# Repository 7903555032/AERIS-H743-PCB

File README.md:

# AERIS-H743 Hardware

# AERIS — Advanced Embedded Research & Intelligent Systems

A 6-layer STM32H743-based embedded development and flight-control/data-logging PCB designed as a practical hardware-design and PCB-layout project.

## Project Status

🚧 **Practice / Learning Project — Hardware Design Completed**

The PCB design phase is complete. This project is primarily a practical exercise to learn and apply professional PCB design concepts using KiCad, including schematic design, component selection, multi-layer stackup, component placement, power distribution, signal routing, high-speed interfaces, sensor interfacing, and design-rule checking.

This is **not a production-ready or professionally validated flight controller**. The design may contain mistakes or areas that require further review, optimization, and hardware validation.

The main goal of this project is to gain hands-on experience designing a complex **6-layer embedded PCB** from the ground up.

## Hardware Features

- STM32H743VIT6 — ARM Cortex-M7, up to 480 MHz
- 6-Layer PCB
- USB Type-C
- SPI / QSPI External Flash
- microSD via SDMMC
- ICM-42688-P IMU
- BME280 Environmental Sensor
- RTC
- INA219 Power Monitor
- CAN FD
- RS485
- GPS UART
- 4× ESC PWM Outputs
- SWD Debug Interface
- 3.3 V / 5 V Regulated Power Architecture

## PCB Architecture

- **L1 — Components + Critical Signals**
- **L2 — Ground Plane**
- **L3 — Power Distribution**
- **L4 — Signal Routing**
- **L5 — Ground Plane**
- **L6 — Bottom Signals + Selected Components**

## Communication Interfaces

- CAN FD
- RS485
- GPS UART
- USB
- SPI / QSPI
- I²C
- SDMMC

## PCB Design Goals

The main purpose of this project is to practice designing a relatively complex embedded PCB and understand how different parts of a real hardware system interact.

The design focuses on:

- 6-layer PCB architecture
- Power distribution
- Ground-plane design
- High-speed digital interfaces
- MCU placement and routing
- Sensor placement
- IMU placement considerations
- QSPI and SDMMC routing
- USB differential-pair routing
- CAN FD and RS485 interfaces
- ESC interfaces
- Thermal and mechanical considerations
- Custom KiCad symbols, footprints and 3D models
- PCB Design Rule Checking (DRC)
- Manufacturing preparation

## Project Structure

```text
AERIS-H743/
│
├── KiCAD/
│   └── AERIS-H743-PCB/
│       ├── AERIS-H743-PCB.kicad_pro
│       ├── AERIS-H743-PCB.kicad_sch
│       ├── AERIS-H743-PCB.kicad_pcb
│       ├── MCU_Core.kicad_sch
│       ├── POWER.kicad_sch
│       ├── Memory&Storage.kicad_sch
│       └── sensors.kicad_sch
│
├── Libraries/
│   ├── Symbols/
│   ├── Footprints.pretty/
│   └── 3D/
│
├── Documentation/
│
├── Datasheets/
│
└── README.md

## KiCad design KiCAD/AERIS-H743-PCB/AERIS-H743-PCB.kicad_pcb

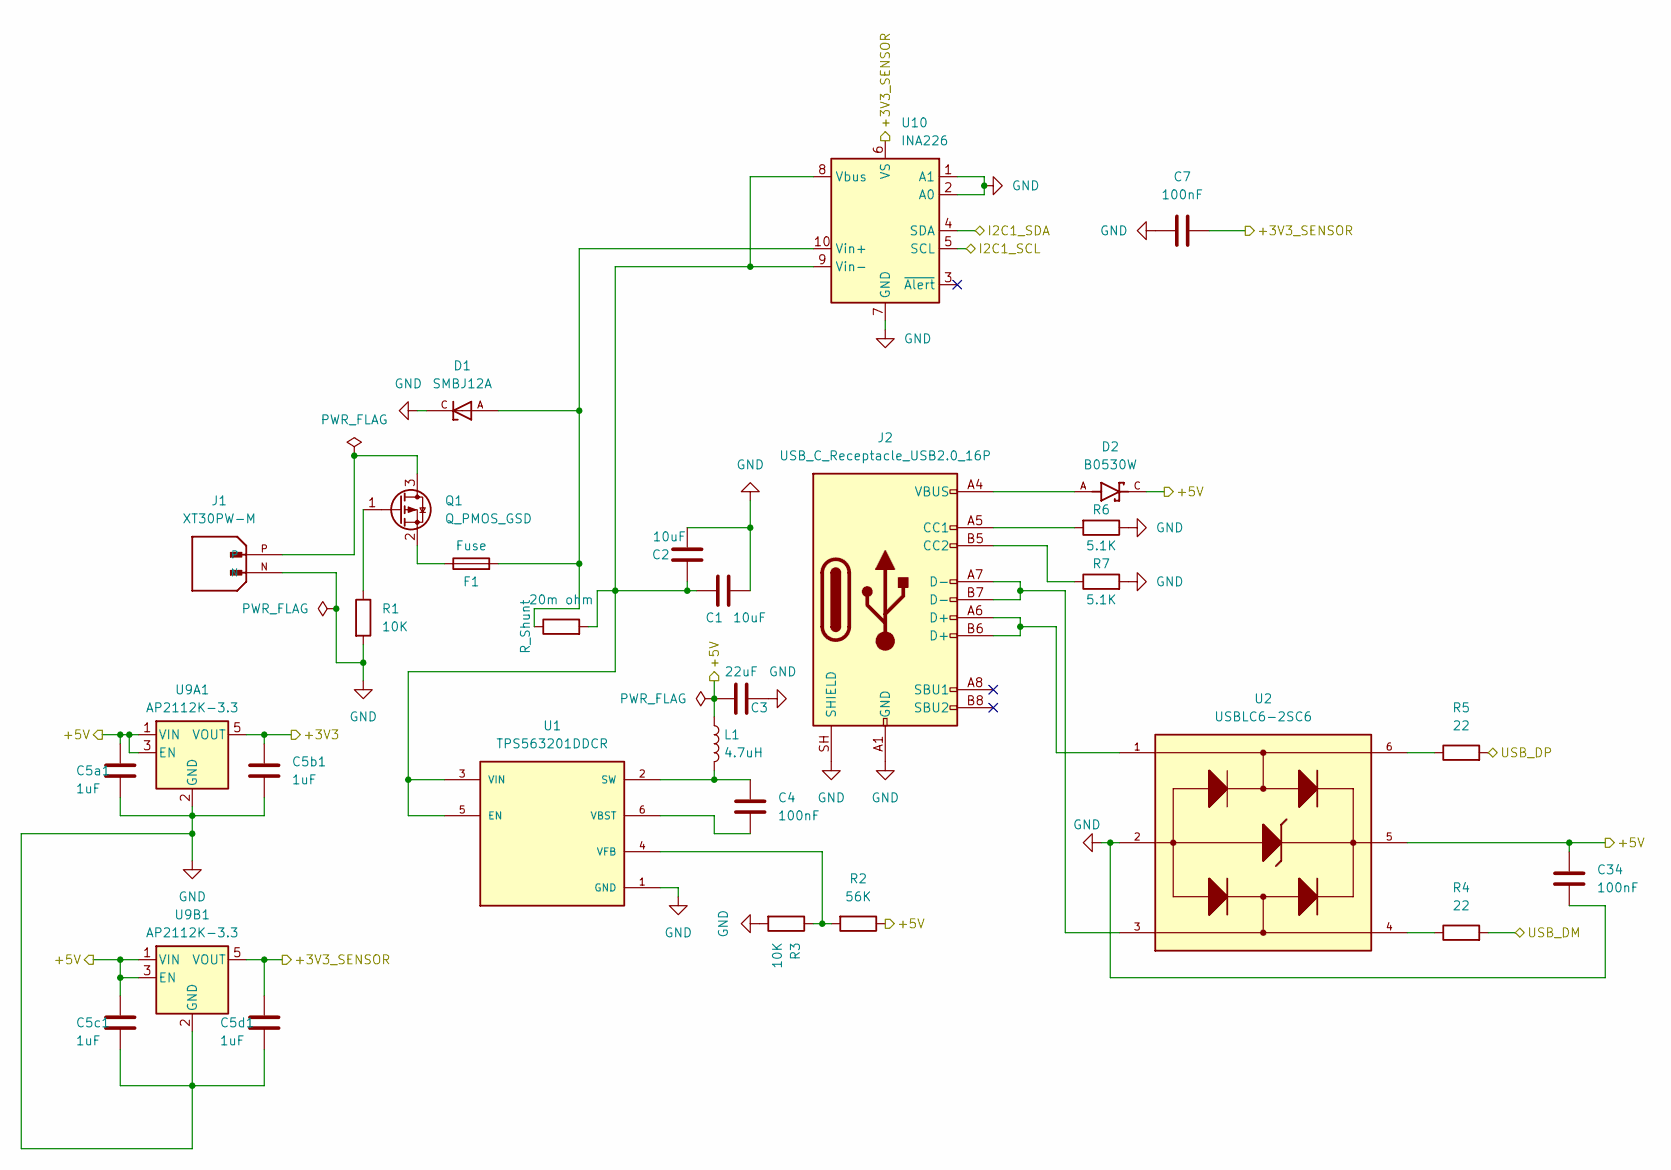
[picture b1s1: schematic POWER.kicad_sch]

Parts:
C1, C2: 10uF; C_0805_2012Metric
C3: 22uF; C_0805_2012Metric
C4, C7: 100nF; C_0805_2012Metric
C5a1, C5b1, C5c1, C5d1: 1uF; C_0805_2012Metric
C34: 100nF; C_0603_1608Metric
D1: SMBJ12A; DIOM4336X265N; PARTREV F2102
D2: B0530W; DIO_B0530W; PARTREV J2112
F1: Fuse; Fuse_1206_3216Metric
J1: XT30PW-M; PARTREV 1.2
J2: USB_C_Receptacle_USB2.0_16P; USB_C_Receptacle_GCT_USB4085
L1: 4.7uH; L_1210_3225Metric
Q1: Q_PMOS_GSD; SOT-23
R1, R3: 10K; R_0603_1608Metric
R2: 56K; R_0603_1608Metric
R4, R5: 22; R_0603_1608Metric
R6, R7: 5.1K; R_0603_1608Metric
R26: 20m ohm; R_2512_6332Metric
U1: TPS563201DDCR; SOT95P280X110-6N; PARTREV December 2015
U2: USBLC6-2SC6; SOT95P280X145-6N
U9A1: AP2112K-3.3; SOT-23-5
U9B1: AP2112K-3.3; SOT95P285X145-5N
U10: INA226; TSSOP-10_3x3mm_P0.5mm

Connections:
/3.3: C5b1.1, U9A1.5 (VOUT); also elsewhere on the board
/3.3_Sensor: C5d1.1, C7.1, U9B1.5 (VOUT), U10.6 (VS); also elsewhere on the board
/I2C1_SCL: U10.5 (SCL); also elsewhere on the board
/I2C1_SDA: U10.4 (SDA); also elsewhere on the board
/USB_DM: R4.2; also elsewhere on the board
/USB_DP: R5.2; also elsewhere on the board
unnamed: D2.A, J2.A4 (VBUS), J2.A9 (VBUS), J2.B4 (VBUS), J2.B9 (VBUS)
unnamed: J2.A5 (CC1), R6.2
unnamed: J2.B5 (CC2), R7.1
unnamed 66: J2.A6 (D+), J2.B6 (D+), U2.1; also elsewhere on the board
unnamed: J1.P, Q1.3 (D)
unnamed: Q1.1 (G), R1.1
unnamed: F1.1, Q1.2 (S)
unnamed 73: R5.1, U2.6; also elsewhere on the board
unnamed 74: C1.1, C2.2, R26.2, U1.3 (VIN), U1.5 (EN), U10.8 (Vbus), U10.9 (Vin-); also elsewhere on the board
unnamed: C4.1, L1.2, U1.2 (SW)
unnamed: C4.2, U1.6 (VBST)
unnamed: R2.2, R3.1, U1.4 (VFB)
unnamed 81: D1.A, F1.2, R26.1, U10.10 (Vin+); also elsewhere on the board

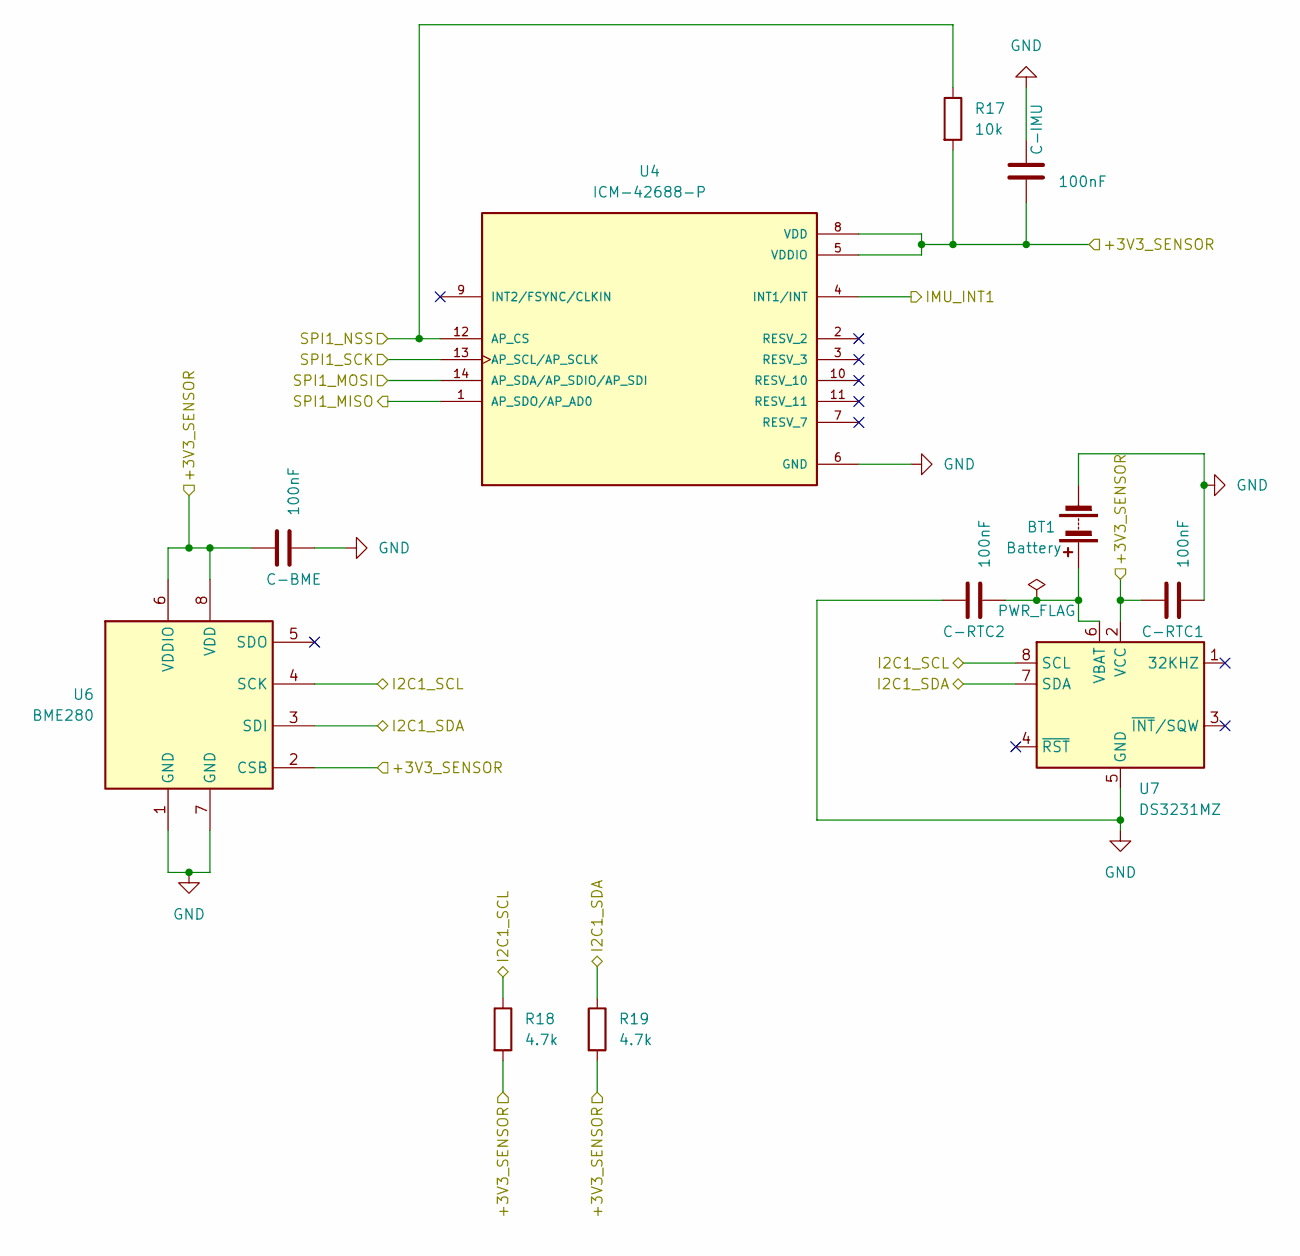
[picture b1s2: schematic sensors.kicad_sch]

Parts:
BT1: Battery; BatteryHolder_Keystone_1058_1x2032
C27, C28, C29, C30: 100nF; C_0603_1608Metric
R17: 10k; R_0603_1608Metric
R18, R19: 4.7k; R_0603_1608Metric
U4: ICM-42688-P; LGA-14_3x2.5mm_P0.5mm_LayoutBorder3x4y; PARTREV 1.2
U6: BME280; Bosch_LGA-8_2.5x2.5mm_P0.65mm_ClockwisePinNumbering
U7: DS3231MZ; SOIC-8_3.9x4.9mm_P1.27mm

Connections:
/3.3_Sensor: C27.2, C28.1, C29.1, R17.2, R18.2, R19.2, U4.5 (VDDIO), U4.8 (VDD), U6.2 (CSB), U6.6 (VDDIO), U6.8 (VDD), U7.2 (VCC); also elsewhere on the board
/I2C1_SCL: R18.1, U6.4 (SCK), U7.8 (SCL); also elsewhere on the board
/I2C1_SDA: R19.1, U6.3 (SDI), U7.7 (SDA); also elsewhere on the board
/IMU_INT1: U4.4 (INT1/INT); also elsewhere on the board
/MCU_Core/SPI1_MISO: U4.1 (AP_SDO/AP_AD0); also elsewhere on the board
/MCU_Core/SPI1_MOSI: U4.14 (AP_SDA/AP_SDIO/AP_SDI); also elsewhere on the board
/MCU_Core/SPI1_NSS: R17.1, U4.12 (AP_CS); also elsewhere on the board
/MCU_Core/SPI1_SCK: U4.13 (AP_SCL/AP_SCLK); also elsewhere on the board
unnamed: BT1.1 (+), C30.2, U7.6 (VBAT)

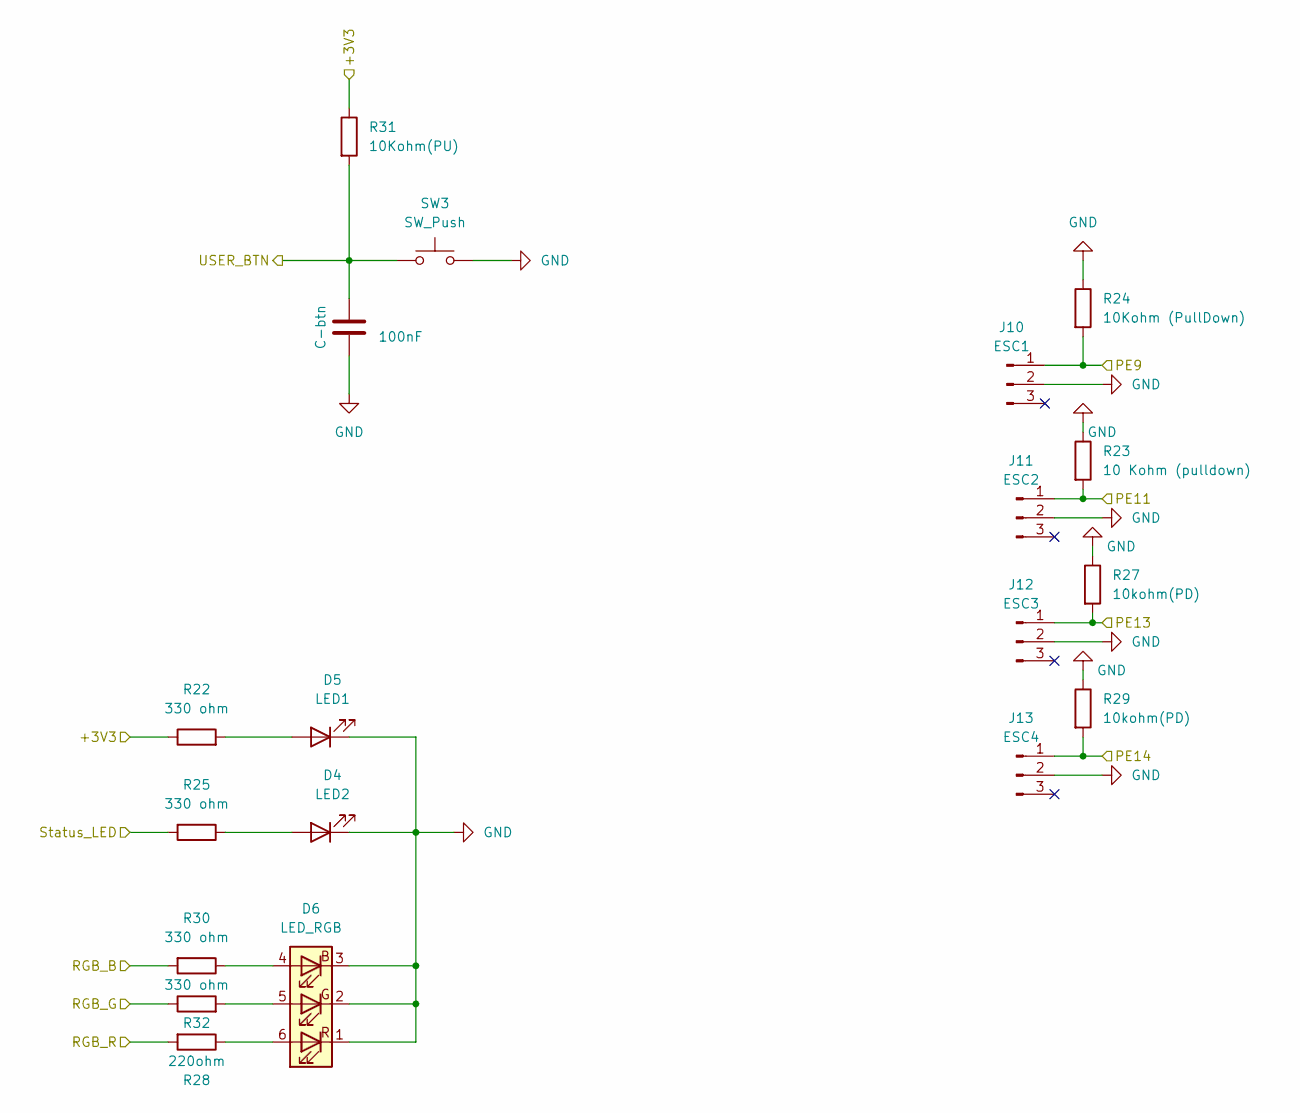
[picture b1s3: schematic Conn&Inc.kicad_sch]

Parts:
C33: 100nF; C_0603_1608Metric
D4: LED2; LED_0603_1608Metric
D5: LED1; LED_0603_1608Metric
D6: LED_RGB; LED_RGB_5050-6
J10: ESC1; PinHeader_1x03_P2.54mm_Vertical
J11: ESC2; PinHeader_1x03_P2.54mm_Vertical
J12: ESC3; PinHeader_1x03_P2.54mm_Vertical
J13: ESC4; PinHeader_1x03_P2.54mm_Vertical
R22, R25, R30, R32: 330 ohm; R_0603_1608Metric
R23: 10 Kohm (pulldown); R_0603_1608Metric
R24: 10Kohm (PullDown); R_0603_1608Metric
R27, R29: 10kohm(PD); R_0603_1608Metric
R28: 220ohm; R_0603_1608Metric
R31: 10Kohm(PU); R_0603_1608Metric
SW3: SW_Push; SW_SPST_B3U-1000P

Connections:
/3.3: R22.1, R31.1; also elsewhere on the board
/PE9: J10.1, R24.2; also elsewhere on the board
/PE11: J11.1, R23.2; also elsewhere on the board
/PE13: J12.1, R27.2; also elsewhere on the board
/PE14: J13.1, R29.2; also elsewhere on the board
/RGB_B: R30.2; also elsewhere on the board
/RGB_G: R32.1; also elsewhere on the board
/RGB_R: R28.2; also elsewhere on the board
/S_LED: R25.2; also elsewhere on the board
/U_BTN: C33.1, R31.2, SW3.1; also elsewhere on the board
unnamed: D4.2 (A), R25.1
unnamed: D5.2 (A), R22.2
unnamed: D6.4 (BA), R30.1
unnamed: D6.5 (GA), R32.2
unnamed: D6.6 (RA), R28.1

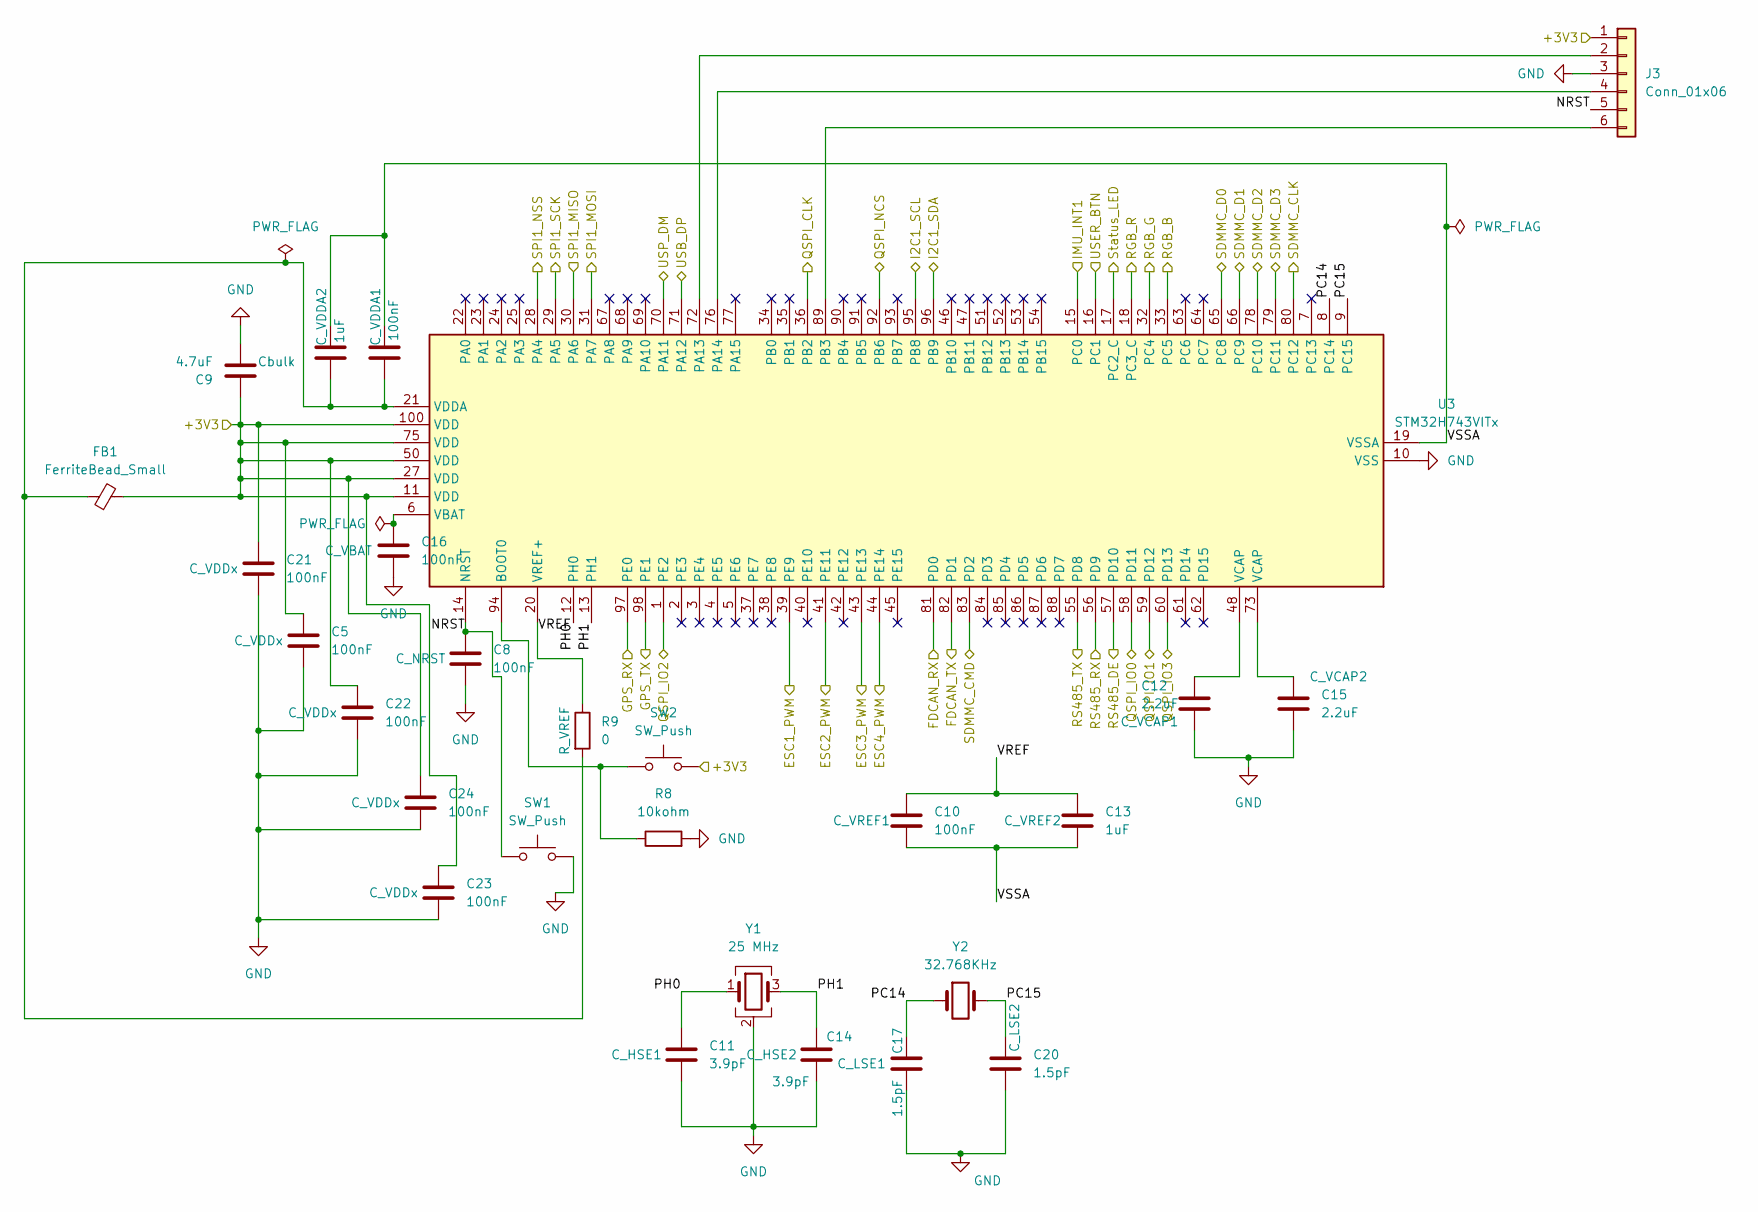
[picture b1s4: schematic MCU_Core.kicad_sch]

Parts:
C5, C8, C10, C16, C18, C21, C22, C23, C24: 100nF; C_0603_1608Metric
C6, C13: 1uF; C_0603_1608Metric
C9: 4.7uF; C_0805_2012Metric
C11, C14: 3.9pF; C_0603_1608Metric
C12, C15: 2.2uF; C_0603_1608Metric
C17, C20: 1.5pF; C_0603_1608Metric
FB1: FerriteBead_Small; L_0603_1608Metric
J3: Conn_01x06; PinHeader_2x03_P1.00mm_Vertical
R8: 10kohm; R_0603_1608Metric
R9: 0; R_0603_1608Metric
SW1, SW2: SW_Push; SW_SPST_B3U-1000P
U3: STM32H743VITx; LQFP-100_14x14mm_P0.5mm
Y1: 25 MHz; Crystal_SMD_3225-4Pin_3.2x2.5mm
Y2: 32.768KHz; Crystal_SMD_3215-2Pin_3.2x1.5mm

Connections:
/3.3: C5.1, C9.1, C21.1, C22.1, C23.1, C24.1, FB1.2, J3.1, SW2.2, U3.11 (VDD), U3.27 (VDD), U3.50 (VDD), U3.75 (VDD), U3.100 (VDD); also elsewhere on the board
/F_RX: U3.81 (PD0); also elsewhere on the board
/F_TX: U3.82 (PD1); also elsewhere on the board
/GPS_RX: U3.97 (PE0); also elsewhere on the board
/GPS_TX: U3.98 (PE1); also elsewhere on the board
/I2C1_SCL: U3.95 (PB8); also elsewhere on the board
/I2C1_SDA: U3.96 (PB9); also elsewhere on the board
/IMU_INT1: U3.15 (PC0); also elsewhere on the board
/MCU_Core/NRST: C8.1, J3.5, SW1.1, U3.14 (NRST)
/MCU_Core/PC14: C17.1, U3.8 (PC14), Y2.1; also elsewhere on the board
/MCU_Core/PC15: C20.1, U3.9 (PC15), Y2.2
/MCU_Core/PH0: C11.1, U3.12 (PH0), Y1.1
/MCU_Core/PH1: C14.1, U3.13 (PH1), Y1.3
/MCU_Core/SPI1_MISO: U3.30 (PA6); also elsewhere on the board
/MCU_Core/SPI1_MOSI: U3.31 (PA7); also elsewhere on the board
/MCU_Core/SPI1_NSS: U3.28 (PA4); also elsewhere on the board
/MCU_Core/SPI1_SCK: U3.29 (PA5); also elsewhere on the board
/MCU_Core/VREF: C10.1, C13.1, R9.1, U3.20 (VREF+)
/MCU_Core/VSSA: C6.1, C10.2, C13.2, C18.2, U3.19 (VSSA)
/PE9: U3.39 (PE9); also elsewhere on the board
/PE11: U3.41 (PE11); also elsewhere on the board
/PE13: U3.43 (PE13); also elsewhere on the board
/PE14: U3.44 (PE14); also elsewhere on the board
/QSPI_CLK: U3.36 (PB2); also elsewhere on the board
/QSPI_IO0: U3.58 (PD11); also elsewhere on the board
/QSPI_IO1: U3.59 (PD12); also elsewhere on the board
/QSPI_IO2: U3.1 (PE2); also elsewhere on the board
/QSPI_IO3: U3.60 (PD13); also elsewhere on the board
/QSPI_NCS: U3.92 (PB6); also elsewhere on the board
/RGB_B: U3.33 (PC5); also elsewhere on the board
/RGB_G: U3.32 (PC4); also elsewhere on the board
/RGB_R: U3.18 (PC3_C); also elsewhere on the board
/RS485_DE: U3.57 (PD10); also elsewhere on the board
/RS485_RX: U3.56 (PD9); also elsewhere on the board
/RS485_TX: U3.55 (PD8); also elsewhere on the board
/SDMMC_CLK: U3.80 (PC12); also elsewhere on the board
/SDMMC_CMD: U3.83 (PD2); also elsewhere on the board
/SDMMC_D0: U3.65 (PC8); also elsewhere on the board
/SDMMC_D1: U3.66 (PC9); also elsewhere on the board
/SDMMC_D2: U3.78 (PC10); also elsewhere on the board
/SDMMC_D3: U3.79 (PC11); also elsewhere on the board
/S_LED: U3.17 (PC2_C); also elsewhere on the board
/USB_DM: U3.70 (PA11); also elsewhere on the board
/USB_DP: U3.71 (PA12); also elsewhere on the board
/U_BTN: U3.16 (PC1); also elsewhere on the board
unnamed: C12.1, U3.48 (VCAP)
unnamed: C15.1, U3.73 (VCAP)
unnamed: J3.2, U3.72 (PA13)
unnamed: J3.4, U3.76 (PA14)
unnamed: J3.6, U3.89 (PB3)
unnamed: R8.1, SW2.1, U3.94 (BOOT0)
unnamed: C16.1, U3.6 (VBAT)
unnamed: C6.2, C18.1, FB1.1, R9.2, U3.21 (VDDA)

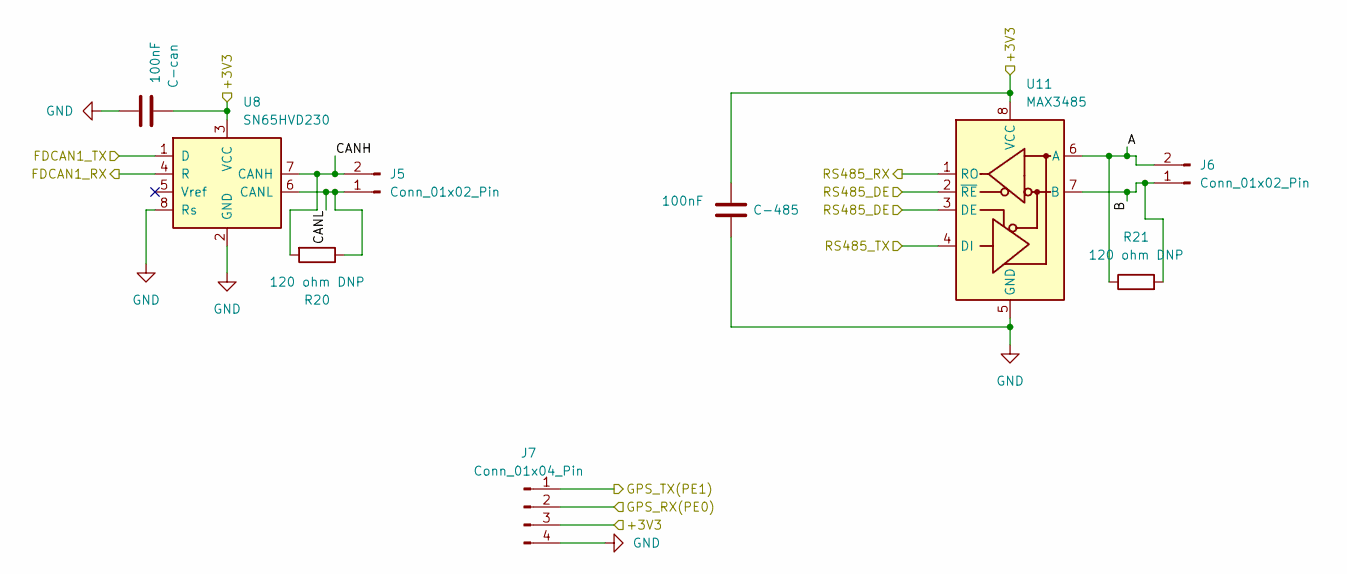
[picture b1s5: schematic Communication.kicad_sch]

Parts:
C31, C32: 100nF; C_0603_1608Metric
J5, J6: Conn_01x02_Pin; PinHeader_1x02_P2.54mm_Vertical
J7: Conn_01x04_Pin; PinHeader_1x04_P2.54mm_Vertical
R20, R21: 120 ohm DNP; R_0603_1608Metric
U8: SN65HVD230; SOIC-8_3.9x4.9mm_P1.27mm
U11: MAX3485; SOIC-8_3.9x4.9mm_P1.27mm

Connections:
/3.3: C31.2, C32.2, J7.3, U8.3 (VCC), U11.8 (VCC); also elsewhere on the board
/COMMUNICATION/A: J6.2, R21.1, U11.6 (A)
/COMMUNICATION/B: J6.1, R21.2, U11.7 (B)
/COMMUNICATION/CANH: J5.2, R20.2, U8.7 (CANH)
/COMMUNICATION/CANL: J5.1, R20.1, U8.6 (CANL)
/F_RX: U8.4 (R); also elsewhere on the board
/F_TX: U8.1 (D); also elsewhere on the board
/GPS_RX: J7.2; also elsewhere on the board
/GPS_TX: J7.1; also elsewhere on the board
/RS485_DE: U11.2 (~RE), U11.3 (DE); also elsewhere on the board
/RS485_RX: U11.1 (RO); also elsewhere on the board
/RS485_TX: U11.4 (DI); also elsewhere on the board

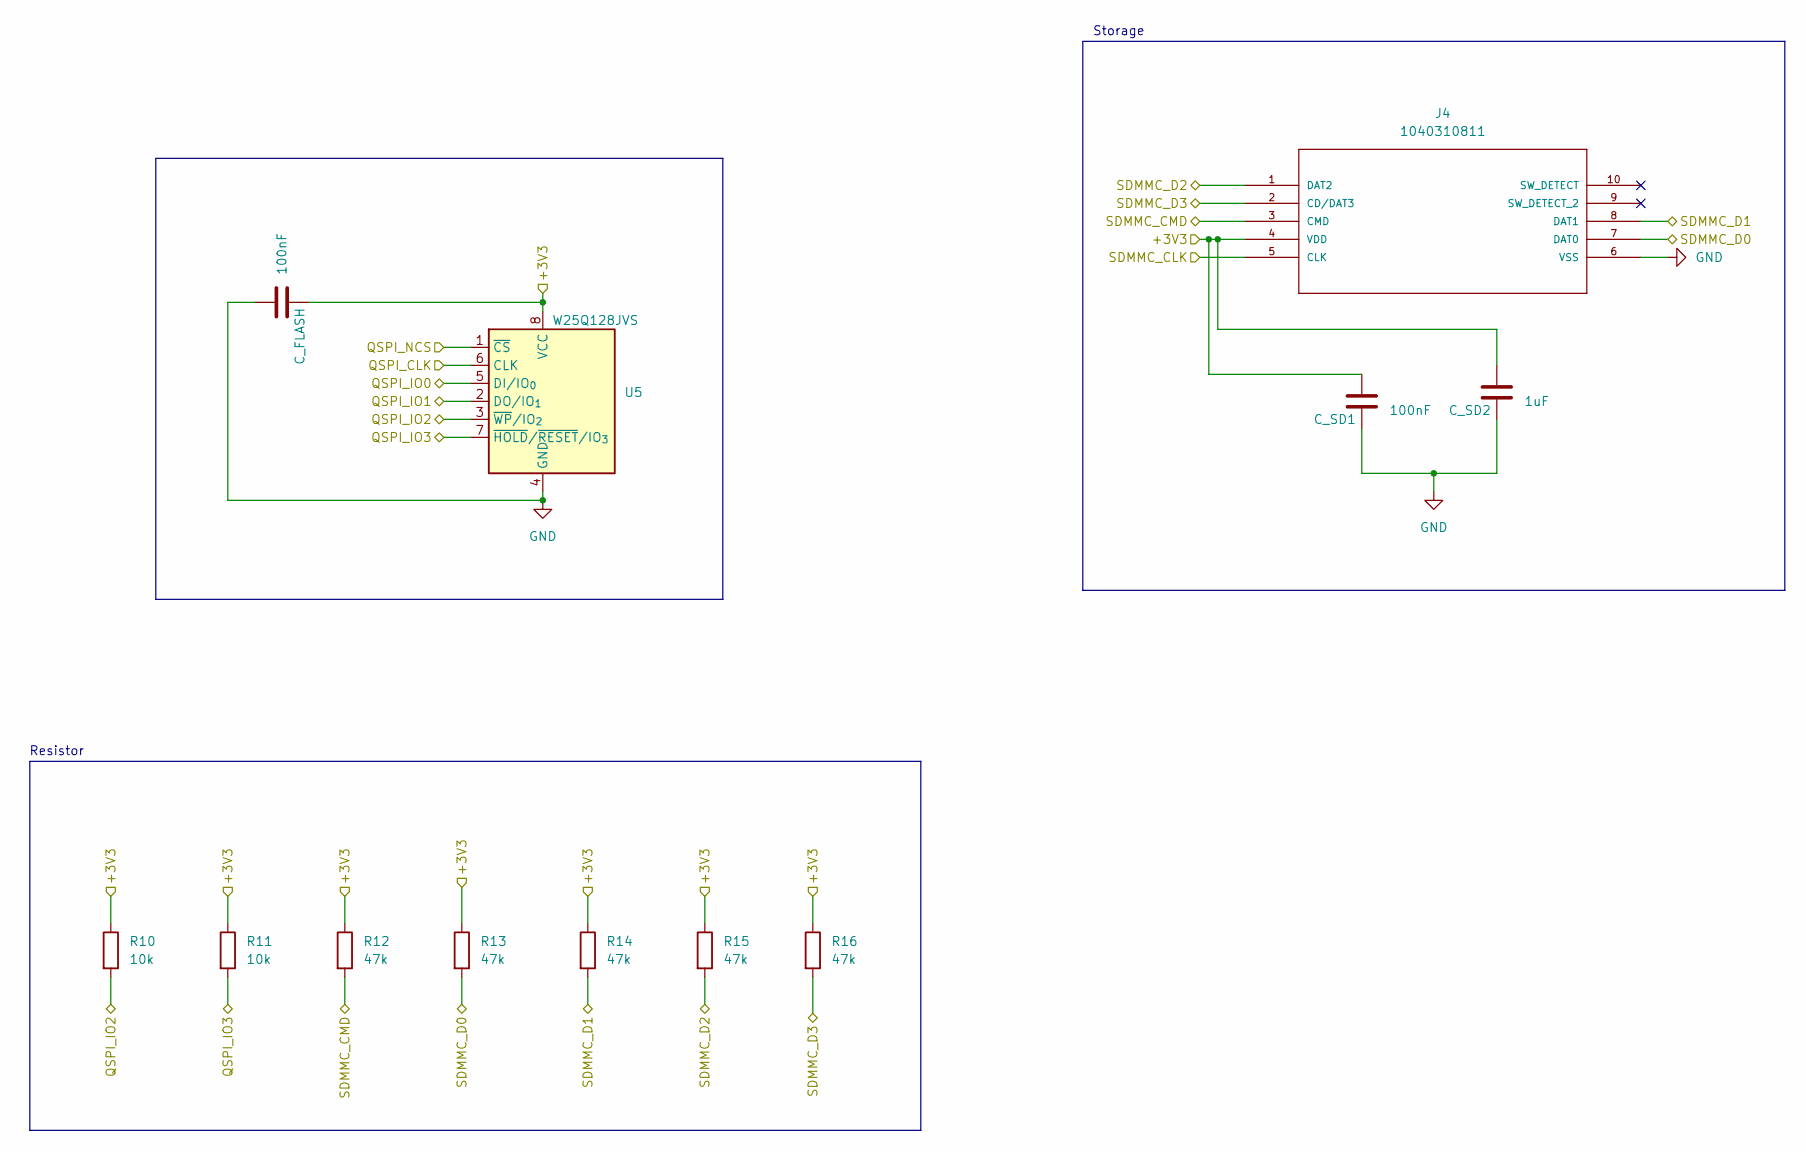
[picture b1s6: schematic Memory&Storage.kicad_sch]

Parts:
C19, C25: 100nF; C_0603_1608Metric
C26: 1uF; C_0603_1608Metric
J4: 1040310811; 104031-0811_MOL; MANUFACTURER_PART_NUMBER 1040310811
R10, R11: 10k; R_0603_1608Metric
R12, R13, R14, R15, R16: 47k; R_0603_1608Metric
U5: W25Q128JVS; SOIC-8_5.3x5.3mm_P1.27mm

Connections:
/3.3: C19.2, C25.1, C26.1, J4.4 (VDD), R10.1, R11.1, R12.1, R13.1, R14.1, R15.1, R16.1, U5.8 (VCC); also elsewhere on the board
/QSPI_CLK: U5.6 (CLK); also elsewhere on the board
/QSPI_IO0: U5.5 (DI/IO_{0}); also elsewhere on the board
/QSPI_IO1: U5.2 (DO/IO_{1}); also elsewhere on the board
/QSPI_IO2: R10.2, U5.3 (~WP/IO_{2}); also elsewhere on the board
/QSPI_IO3: R11.2, U5.7 (~HOLD/~RESET/IO_{3}); also elsewhere on the board
/QSPI_NCS: U5.1 (~CS); also elsewhere on the board
/SDMMC_CLK: J4.5 (CLK); also elsewhere on the board
/SDMMC_CMD: J4.3 (CMD), R12.2; also elsewhere on the board
/SDMMC_D0: J4.7 (DAT0), R13.2; also elsewhere on the board
/SDMMC_D1: J4.8 (DAT1), R14.2; also elsewhere on the board
/SDMMC_D2: J4.1 (DAT2), R15.2; also elsewhere on the board
/SDMMC_D3: J4.2 (CD/DAT3), R16.2; also elsewhere on the board

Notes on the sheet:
Storage
Resistor

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
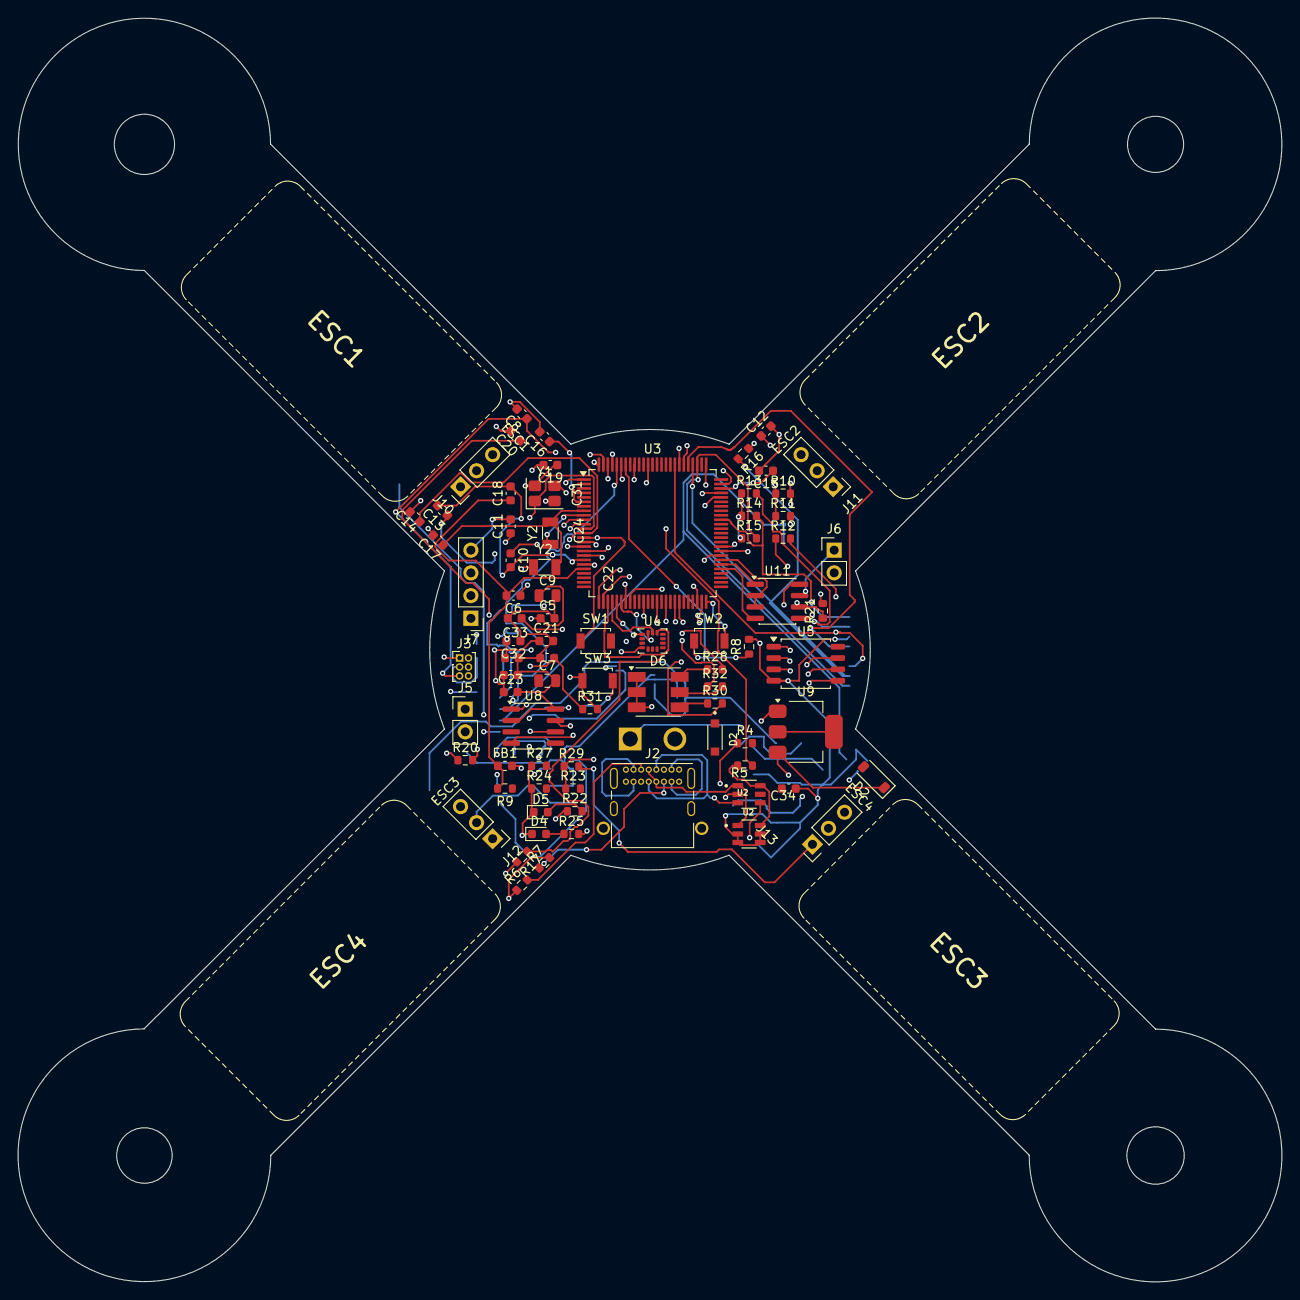
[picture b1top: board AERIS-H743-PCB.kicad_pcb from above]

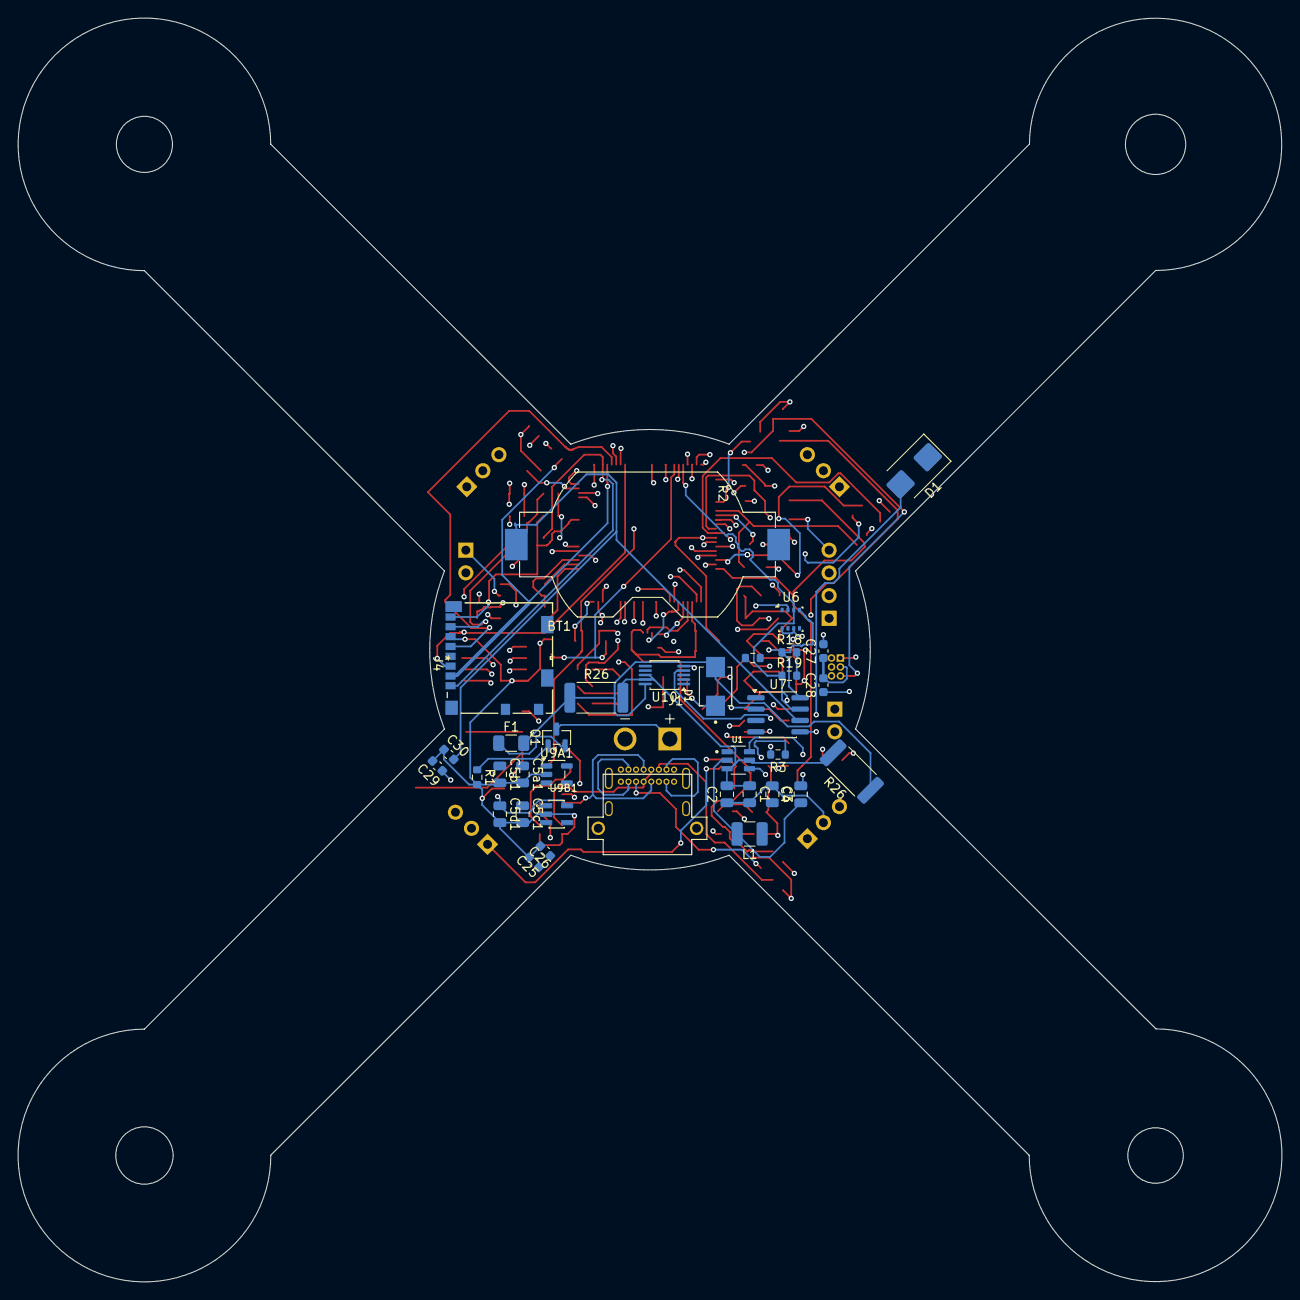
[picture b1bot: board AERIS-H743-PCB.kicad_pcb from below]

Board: 6 copper layers, 141.4 x 141.4 mm, 114 parts (35 on the bottom side), 83 nets.

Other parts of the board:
D1#2: D_TVS; D_SMB
D2#2: D_Schottky; D_SOD-123
R26#2: 20mohm; R_2512_6332Metric
U2#2: USBLC6-2SC6; SOT95P280X145-6N
U9: AMS1117-3.3; SOT-223-3_TabPin2
Y2#2: 32.768kHz; Crystal_SMD_3215-2Pin_3.2x1.5mm

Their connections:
/MCU_Core/PC14: Y2#2.1; also elsewhere on the board
/POWER SECTION/5V: D2#2.1 (K), U9.3 (VI)
/POWER SECTION/GND: D1#2.2 (A2), U9.1 (GND)
unnamed 66: U2#2.1; also elsewhere on the board
unnamed 73: U2#2.6; also elsewhere on the board
unnamed 74: R26#2.2; also elsewhere on the board
unnamed 81: R26#2.1; also elsewhere on the board
